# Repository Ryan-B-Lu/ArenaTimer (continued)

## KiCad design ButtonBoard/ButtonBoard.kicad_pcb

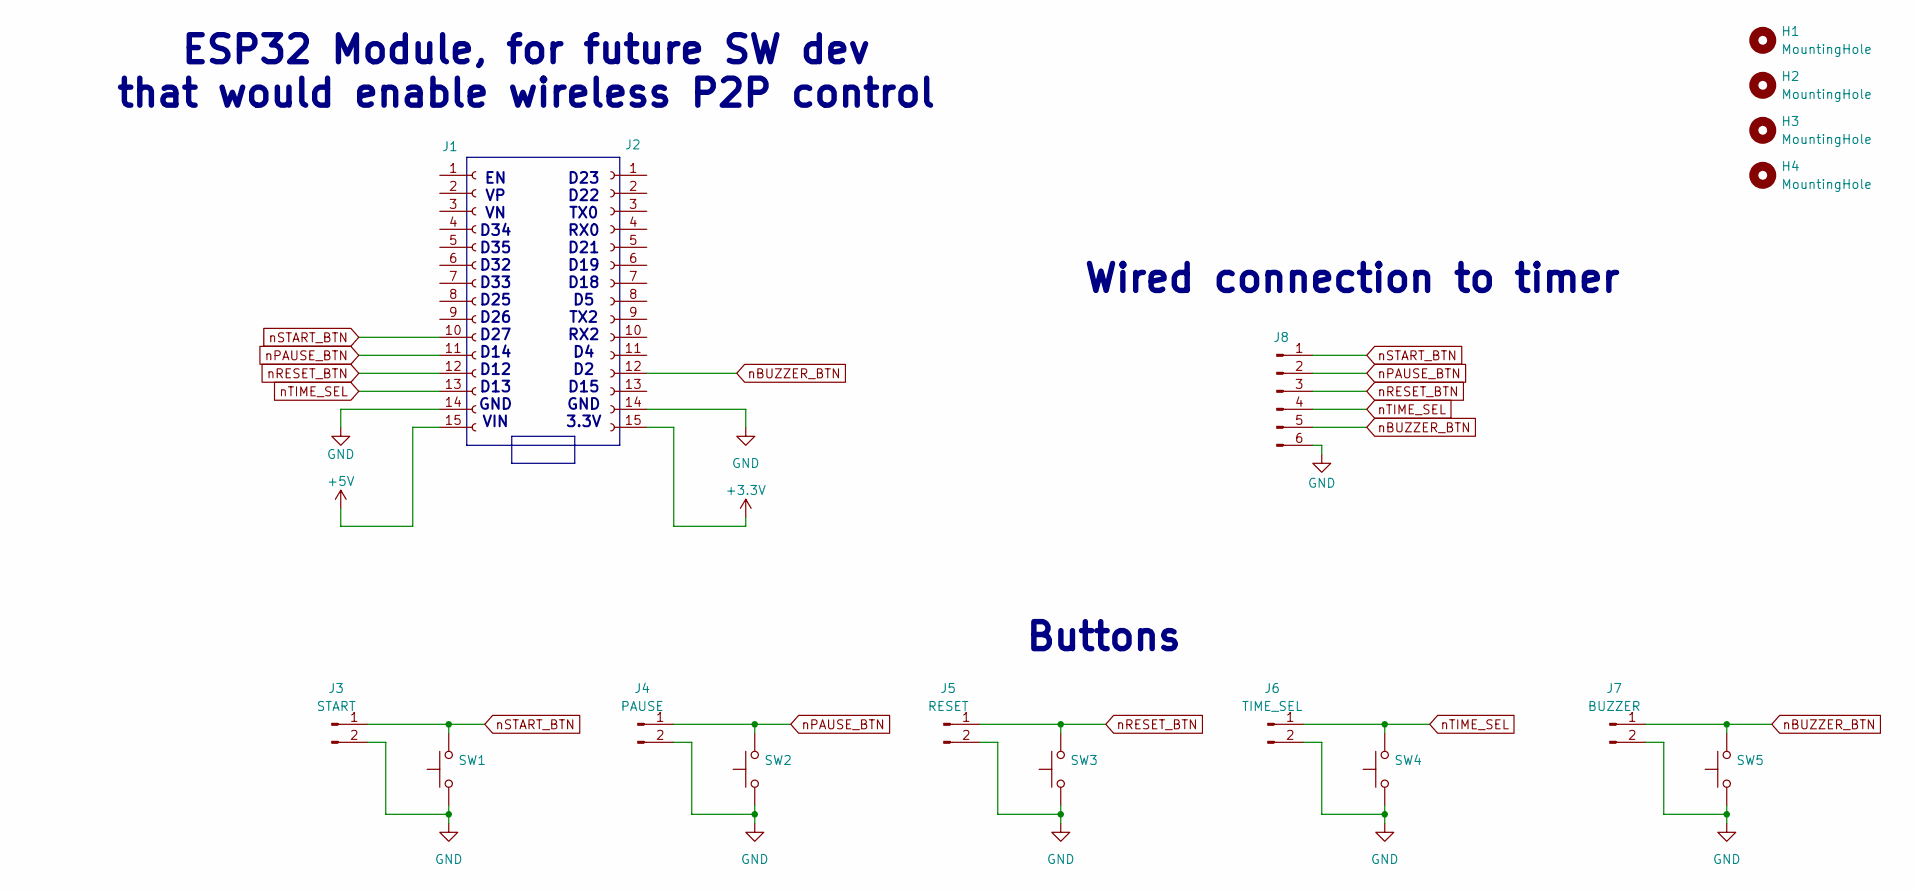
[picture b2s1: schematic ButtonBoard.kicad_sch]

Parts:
H1, H2, H3, H4: MountingHole; MountingHole_3.2mm_M3
J1, J2: Conn_01x15_Socket; PinSocket_1x15_P2.54mm_Vertical; LCSC C124408
J3: START; PinHeader_1x02_P2.54mm_Vertical
J4: PAUSE; PinHeader_1x02_P2.54mm_Vertical
J5: RESET; PinHeader_1x02_P2.54mm_Vertical
J6: TIME_SEL; PinHeader_1x02_P2.54mm_Vertical
J7: BUZZER; PinHeader_1x02_P2.54mm_Vertical
J8: Conn_01x06_Pin; JST_EH_S6B-EH_1x06_P2.50mm_Horizontal
SW1: START; SW_PUSH-12mm; LCSC C5377619
SW2: PAUSE; SW_PUSH-12mm; LCSC C5377619
SW3: RESET; SW_PUSH-12mm; LCSC C5377619
SW4: TIME_SEL; SW_PUSH-12mm; LCSC C5377619
SW5: BUZZER; SW_PUSH-12mm; LCSC C5377619

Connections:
+3.3V: J2.15
+5V: J1.15
GND: J1.14, J2.14, J3.2, J4.2, J5.2, J6.2, J7.2, J8.6, SW1.1, SW2.1, SW3.1, SW4.1, SW5.1
nBUZZER_BTN: J2.12, J7.1, J8.5, SW5.2
nPAUSE_BTN: J1.11, J4.1, J8.2, SW2.2
nRESET_BTN: J1.12, J5.1, J8.3, SW3.2
nSTART_BTN: J1.10, J3.1, J8.1, SW1.2
nTIME_SEL: J1.13, J6.1, J8.4, SW4.2

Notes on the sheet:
ESP32 Module, for future SW dev that would enable wireless P2P control
D23 D22 TX0 RX0 D21 D19 D18 D5 TX2 RX2 D4 D2 D15 GND 3.3V
Wired connection to timer
Buttons
EN VP VN D34 D35 D32 D33 D25 D26 D27 D14 D12 D13 GND VIN

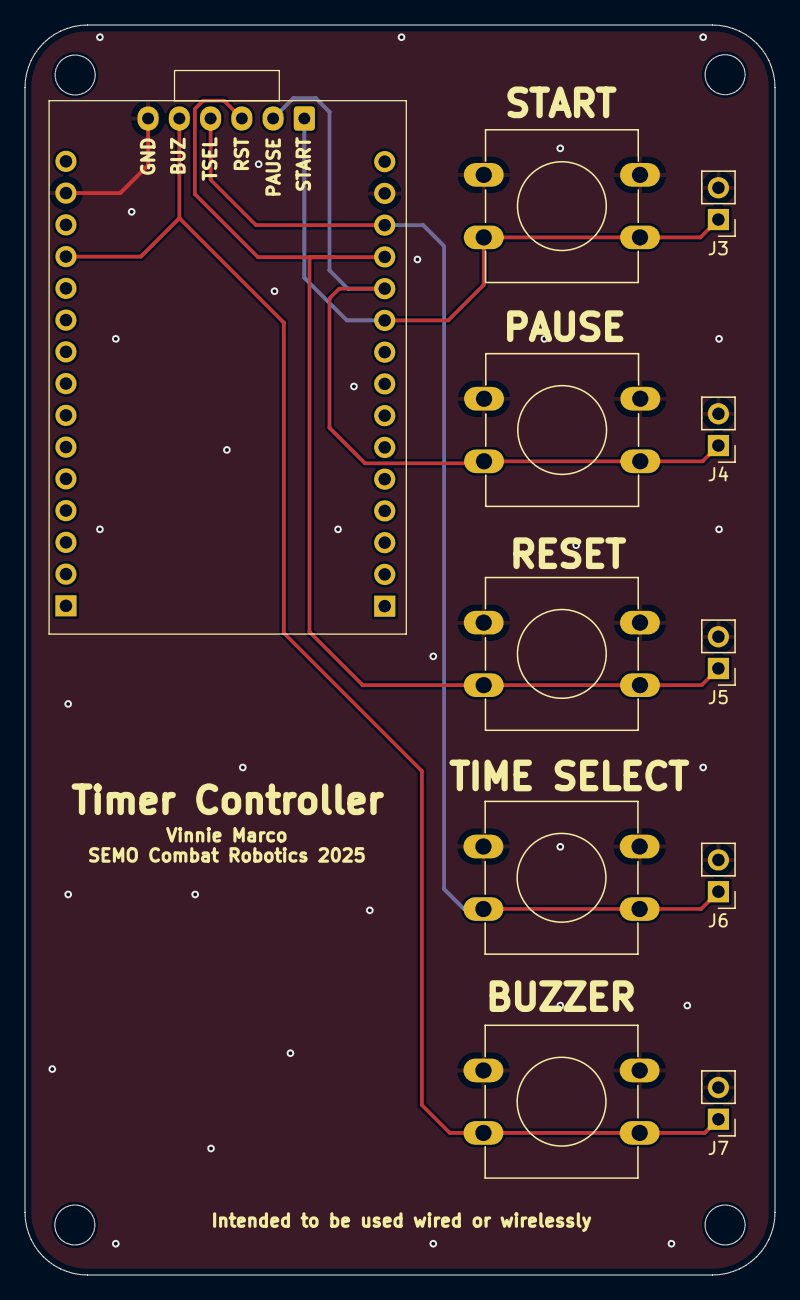
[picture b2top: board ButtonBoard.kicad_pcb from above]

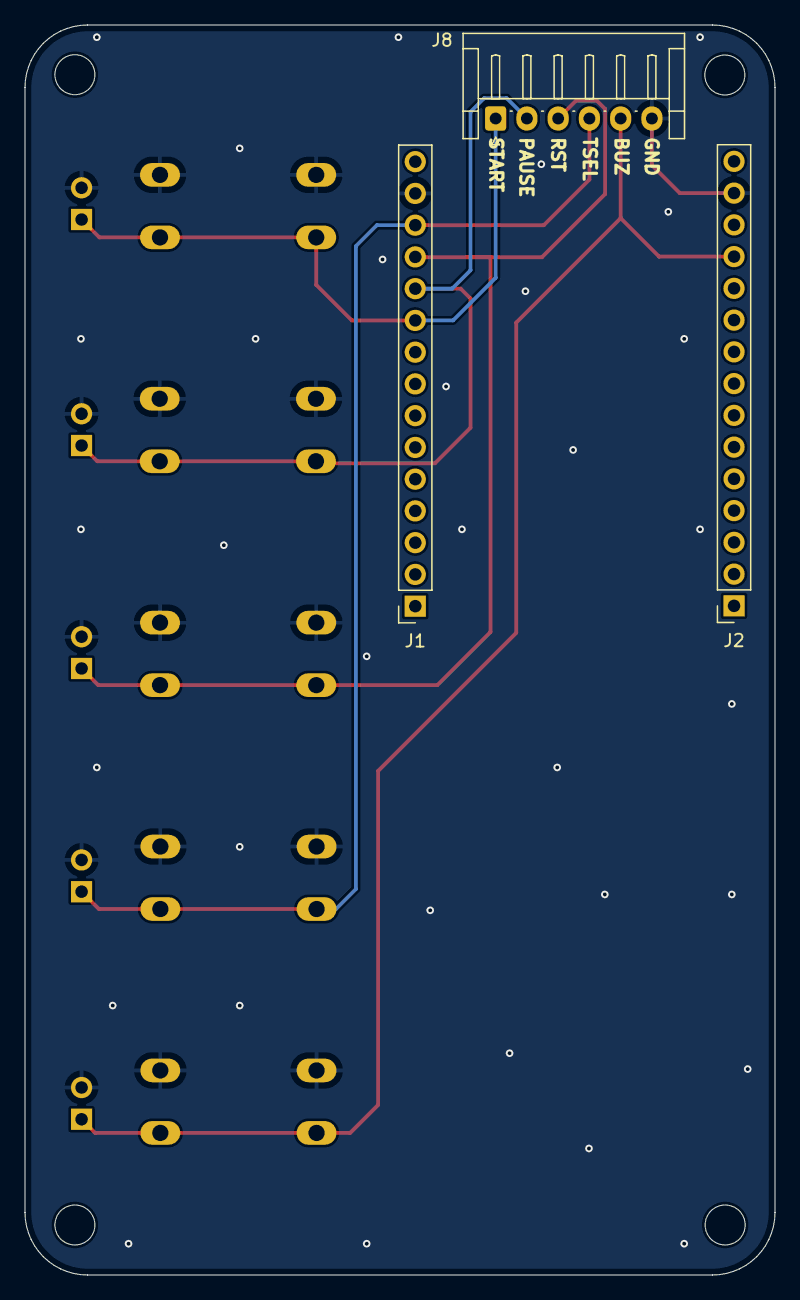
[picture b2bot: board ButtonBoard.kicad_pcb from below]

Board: 2 copper layers, 60.0 x 100.0 mm, 17 parts (3 on the bottom side), 6 nets.

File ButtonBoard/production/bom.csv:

Designator,Footprint,Quantity,Value,LCSC Part #
"J1, J2",PinSocket_1x15_P2.54mm_Vertical,2,Conn_01x15_Socket,C124408
J3,PinHeader_1x02_P2.54mm_Vertical,1,START,
J4,PinHeader_1x02_P2.54mm_Vertical,1,PAUSE,
J5,PinHeader_1x02_P2.54mm_Vertical,1,RESET,
J6,PinHeader_1x02_P2.54mm_Vertical,1,TIME_SEL,
J7,PinHeader_1x02_P2.54mm_Vertical,1,BUZZER,
J8,JST_EH_S6B-EH_1x06_P2.50mm_Horizontal,1,Conn_01x06_Pin,
SW1,SW_PUSH-12mm,1,START,C5377619
SW2,SW_PUSH-12mm,1,PAUSE,C5377619
SW3,SW_PUSH-12mm,1,RESET,C5377619
SW4,SW_PUSH-12mm,1,TIME_SEL,C5377619
SW5,SW_PUSH-12mm,1,BUZZER,C5377619

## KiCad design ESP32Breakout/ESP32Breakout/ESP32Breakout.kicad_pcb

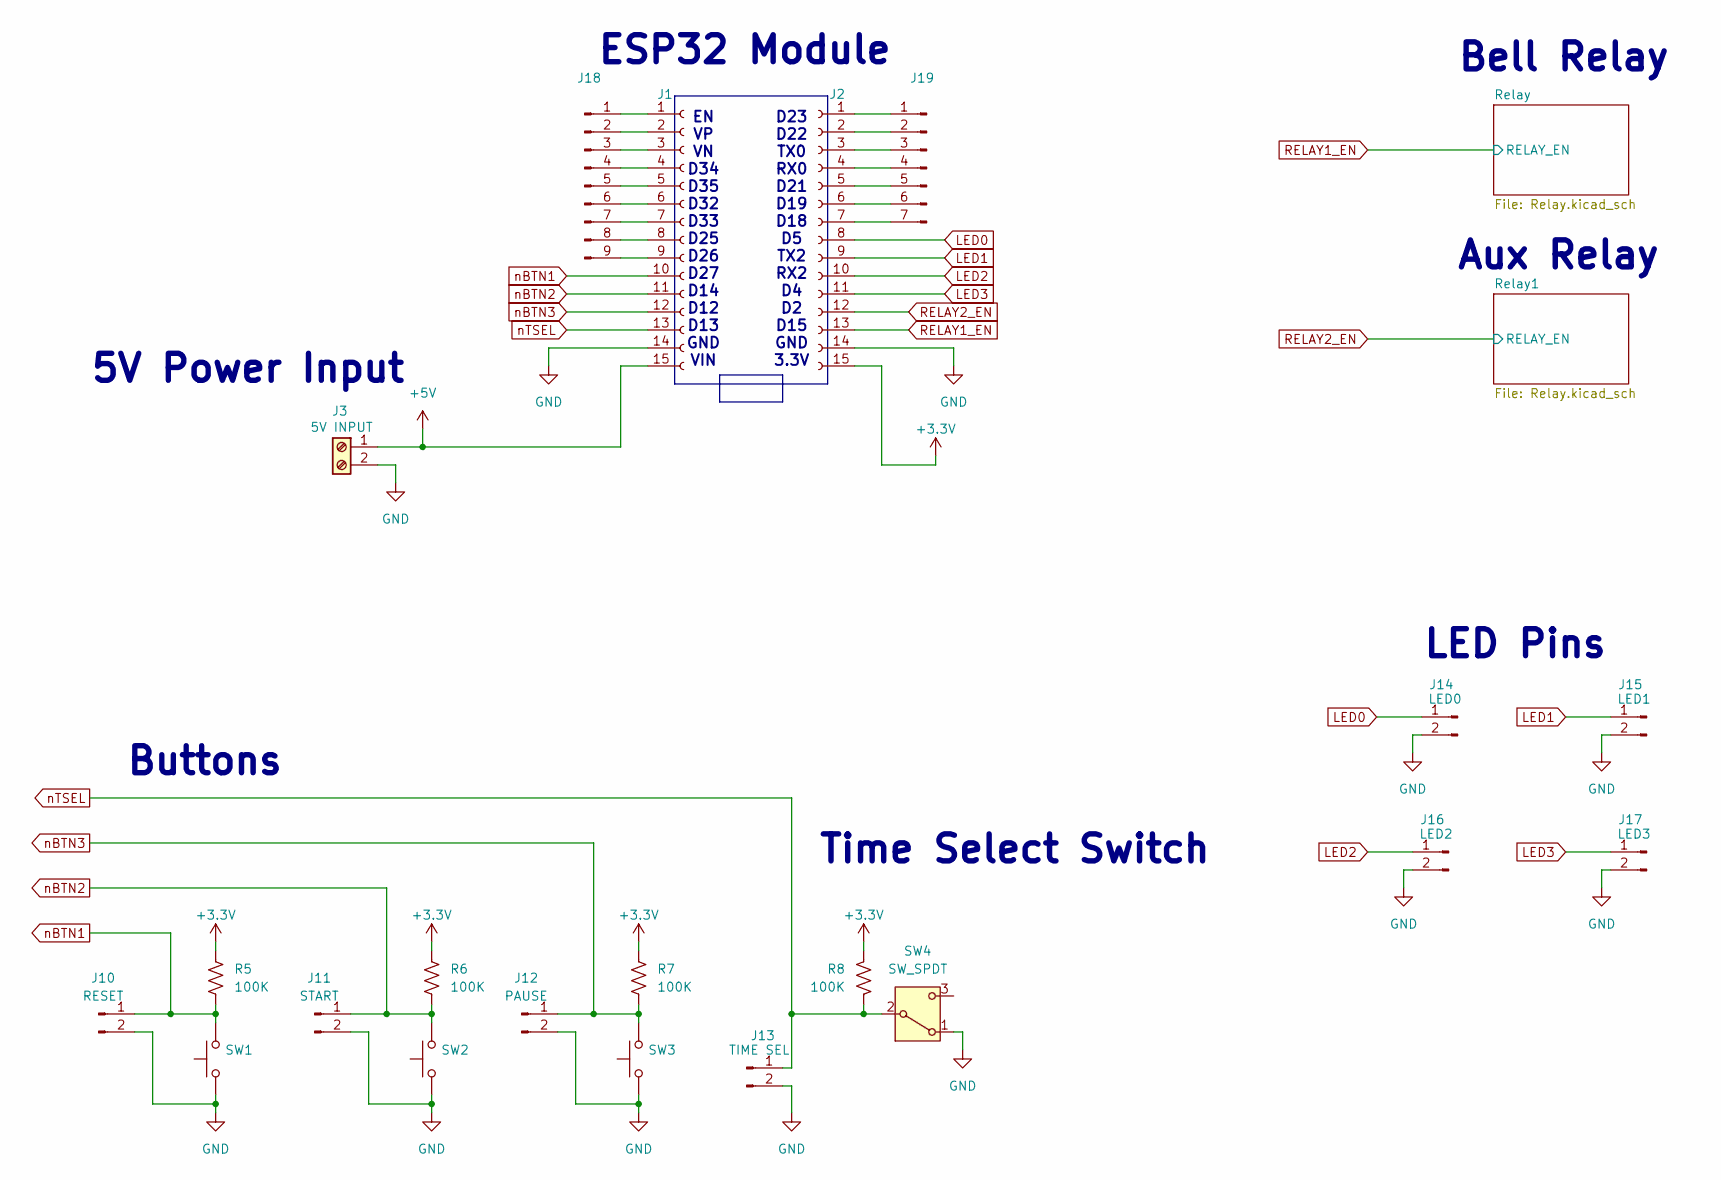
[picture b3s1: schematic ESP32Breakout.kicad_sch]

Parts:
J1, J2: Conn_01x15_Socket; PinHeader_1x15_P2.54mm_Vertical; LCSC C124408
J3: 5V INPUT; TerminalBlock_bornier-2_P5.08mm; LCSC C5142622
J10: RESET; PinHeader_1x02_P2.54mm_Vertical
J11: START; PinHeader_1x02_P2.54mm_Vertical
J12: PAUSE; PinHeader_1x02_P2.54mm_Vertical
J13: TIME SEL; PinHeader_1x02_P2.54mm_Vertical
J14: LED0; PinHeader_1x02_P2.54mm_Vertical; LCSC C124375
J15: LED1; PinHeader_1x02_P2.54mm_Vertical; LCSC C124375
J16: LED2; PinHeader_1x02_P2.54mm_Vertical; LCSC C124375
J17: LED3; PinHeader_1x02_P2.54mm_Vertical; LCSC C124375
J18: Conn_01x09_Pin; PinHeader_1x09_P2.54mm_Vertical
J19: Conn_01x07_Pin; PinHeader_1x07_P2.54mm_Vertical
R5, R6, R7, R8: 100K; R_0402_1005Metric; LCSC C25530
SW1: RESET; SW_PUSH-12mm; LCSC C5377619
SW2: START; SW_PUSH-12mm; LCSC C5377619
SW3: PAUSE; SW_PUSH-12mm; LCSC C5377619
SW4: SW_SPDT; SW_CK_JS202011AQN_DPDT_Angled; LCSC C223857

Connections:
+3.3V: J2.15, R5.1, R6.1, R7.1, R8.1
+5V: J1.15, J3.1; also elsewhere on the board
GND: J1.14, J2.14, J3.2, J10.2, J11.2, J12.2, J13.2, J14.2, J15.2, J16.2, J17.2, SW1.1, SW2.1, SW3.1, SW4.1 (A); also elsewhere on the board
LED0: J2.8, J14.1
LED1: J2.9, J15.1
LED2: J2.10, J16.1
LED3: J2.11, J17.1
unnamed: J1.1, J18.1
unnamed: J1.2, J18.2
unnamed: J1.3, J18.3
unnamed: J1.4, J18.4
unnamed: J1.5, J18.5
unnamed: J1.6, J18.6
unnamed: J1.7, J18.7
unnamed: J1.8, J18.8
unnamed: J1.9, J18.9
unnamed: J2.1, J19.1
unnamed: J2.2, J19.2
unnamed: J2.3, J19.3
unnamed: J2.4, J19.4
unnamed: J2.5, J19.5
unnamed: J2.6, J19.6
unnamed: J2.7, J19.7
RELAY1_EN: J2.13; also elsewhere on the board
RELAY2_EN: J2.12; also elsewhere on the board
nBTN1: J1.10, J10.1, R5.2, SW1.2
nBTN2: J1.11, J11.1, R6.2, SW2.2
nBTN3: J1.12, J12.1, R7.2, SW3.2
nTSEL: J1.13, J13.1, R8.2, SW4.2 (B)

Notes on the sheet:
Time Select Switch
5V Power Input
ESP32 Module
EN VP VN D34 D35 D32 D33 D25 D26 D27 D14 D12 D13 GND VIN
LED Pins
Bell Relay
D23 D22 TX0 RX0 D21 D19 D18 D5 TX2 RX2 D4 D2 D15 GND 3.3V
Aux Relay
Buttons

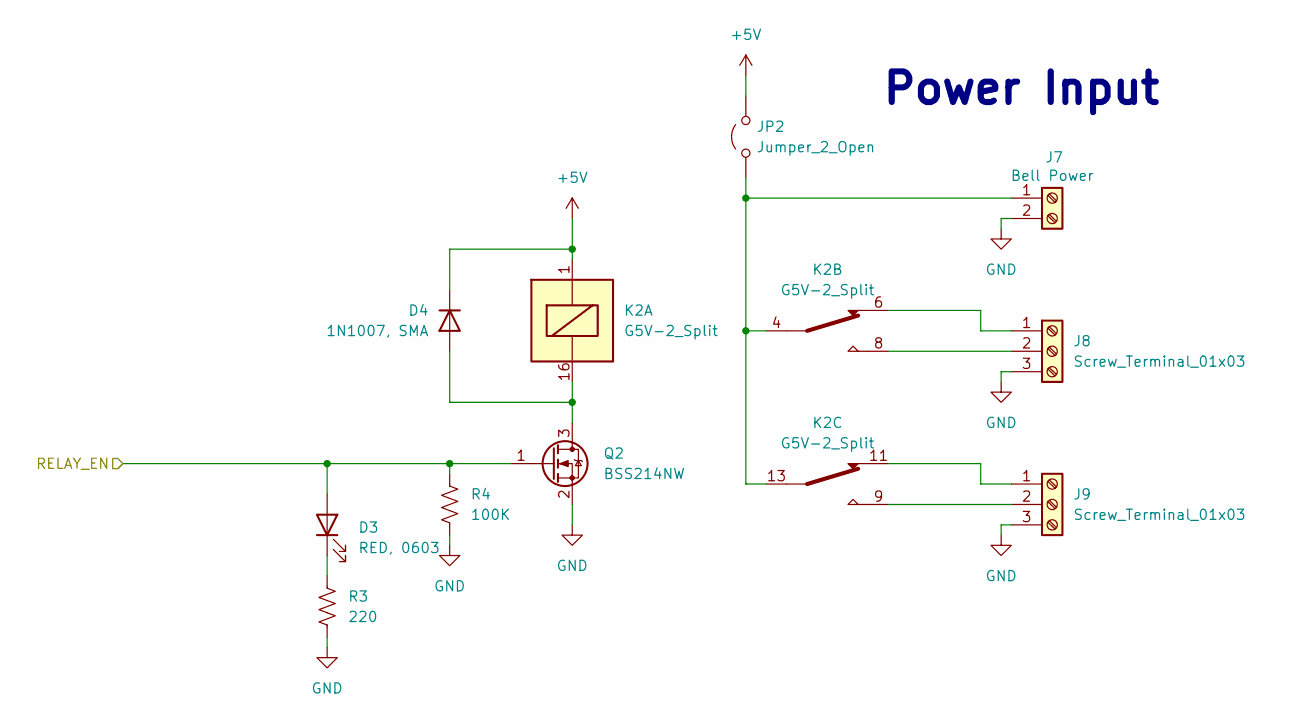
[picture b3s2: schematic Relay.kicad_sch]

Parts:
D3: RED, 0603; LED_0603_1608Metric; LCSC C2286
D4: 1N1007, SMA; D_SMA; LCSC C727081
J7: Bell Power; TerminalBlock_bornier-2_P5.08mm; LCSC C5142622
J8, J9: Screw_Terminal_01x03; TerminalBlock_bornier-3_P5.08mm; LCSC C5142621
JP2: Jumper_2_Open; SolderJumper-2_P1.3mm_Open_RoundedPad1.0x1.5mm
K2: G5V-2_Split; Relay_DPDT_Omron_G5V-2; LCSC C27269
Q2: BSS214NW; SOT-323_SC-70; LCSC C412741
R3: 220; R_0402_1005Metric; LCSC C25091
R4: 100K; R_0402_1005Metric; LCSC C25530

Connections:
+5V: D4.1 (K), JP2.2 (B), K2.1; also elsewhere on the board
GND: J7.2, J8.3, J9.3, Q2.2 (S), R3.2, R4.2; also elsewhere on the board
unnamed: D3.1 (K), R3.1
unnamed: D4.2 (A), K2.16, Q2.3 (D)
unnamed: J7.1, JP2.1 (A), K2.4, K2.13
unnamed: J8.1, K2.6
unnamed: J8.2, K2.8
unnamed: J9.1, K2.11
unnamed: J9.2, K2.9
RELAY2_EN: D3.2 (A), Q2.1 (G), R4.1; also elsewhere on the board

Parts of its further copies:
D1: RED, 0603; LED_0603_1608Metric; LCSC C2286
D2: 1N1007, SMA; D_SMA; LCSC C727081
J4: Bell Power; TerminalBlock_bornier-2_P5.08mm; LCSC C5142622
J5, J6: Screw_Terminal_01x03; TerminalBlock_bornier-3_P5.08mm; LCSC C5142621
JP1: Jumper_2_Open; SolderJumper-2_P1.3mm_Open_RoundedPad1.0x1.5mm
K1: G5V-2_Split; Relay_DPDT_Omron_G5V-2; LCSC C27269
Q1: BSS214NW; SOT-323_SC-70; LCSC C412741
R1: 220; R_0402_1005Metric; LCSC C25091
R2: 100K; R_0402_1005Metric; LCSC C25530

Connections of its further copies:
+5V: D2.1 (K), JP1.2 (B), K1.1; also elsewhere on the board
GND: J4.2, J5.3, J6.3, Q1.2 (S), R1.2, R2.2; also elsewhere on the board
unnamed: D1.1 (K), R1.1
unnamed: D2.2 (A), K1.16, Q1.3 (D)
unnamed: J4.1, JP1.1 (A), K1.4, K1.13
unnamed: J5.1, K1.6
unnamed: J5.2, K1.8
unnamed: J6.1, K1.11
unnamed: J6.2, K1.9
RELAY1_EN: D1.2 (A), Q1.1 (G), R2.1; also elsewhere on the board

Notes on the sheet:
Power Input

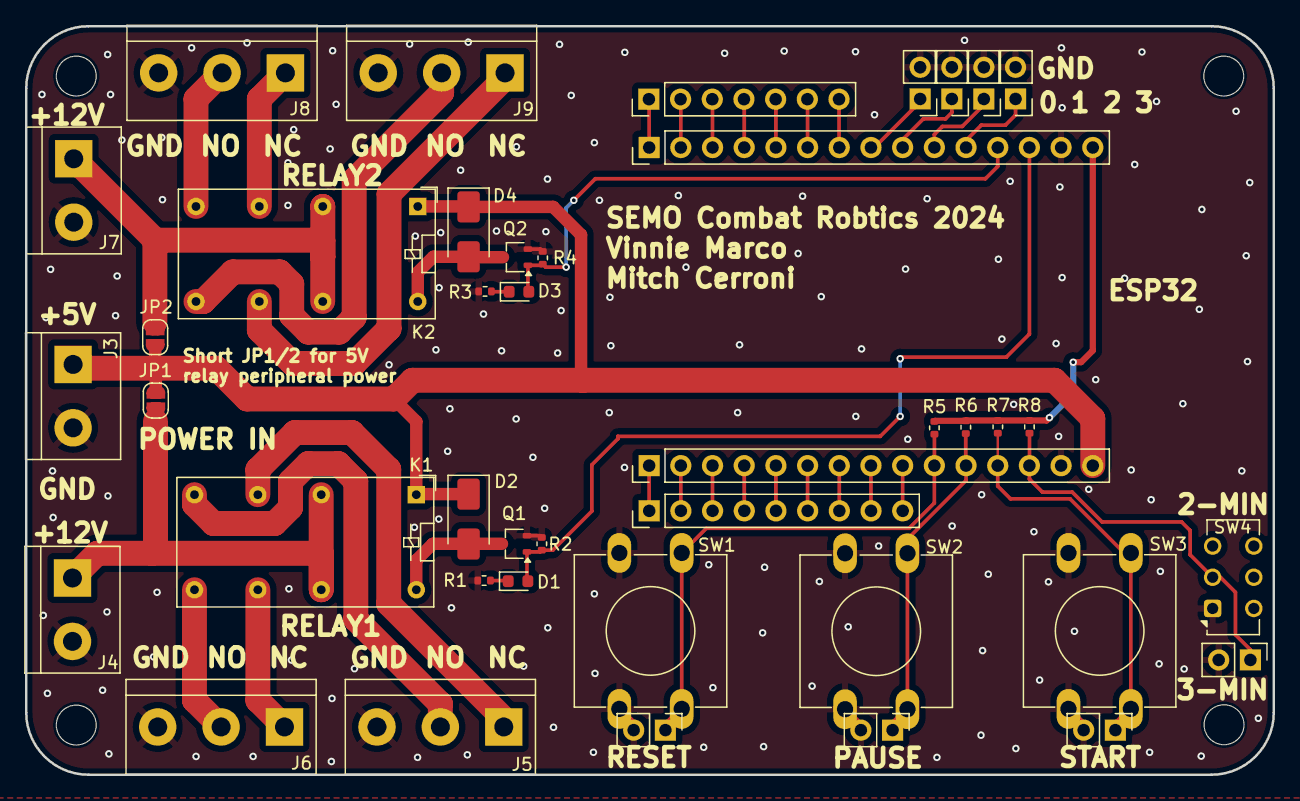
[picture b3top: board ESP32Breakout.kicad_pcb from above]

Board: 2 copper layers, 100.0 x 60.0 mm, 41 parts (0 on the bottom side), 43 nets.

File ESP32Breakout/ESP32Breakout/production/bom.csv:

Designator,Footprint,Quantity,Value,LCSC Part #
"D1, D3",0603,2,"RED, 0603", C2286
"D2, D4",D_SMA,2,"1N1007, SMA",C727081
"J1, J2",PinHeader_1x15_P2.54mm_Vertical,2,Conn_01x15_Socket,C124408
J13,PinHeader_1x02_P2.54mm_Vertical,1,TIME SEL,
J14,PinHeader_1x02_P2.54mm_Vertical,1,LED0,C124375
J15,PinHeader_1x02_P2.54mm_Vertical,1,LED1,C124375
J16,PinHeader_1x02_P2.54mm_Vertical,1,LED2,C124375
J17,PinHeader_1x02_P2.54mm_Vertical,1,LED3,C124375
J3,TerminalBlock_bornier-2_P5.08mm,1,5V INPUT,C5142622
"J4, J7",TerminalBlock_bornier-2_P5.08mm,2,Bell Power,C5142622
"J5, J6, J8, J9",TerminalBlock_bornier-3_P5.08mm,4,Screw_Terminal_01x03,C5142621
"JP1, JP2",SolderJumper-2_P1.3mm_Open_RoundedPad1.0x1.5mm,2,Jumper_2_Open,
"K1, K2",Relay_DPDT_Omron_G5V-2,2,G5V-2_Split,C27269
"Q1, Q2",SOT-323_SC-70,2,BSS214NW,C412741
"R1, R3",0402,2,220,C25091
"R2, R4, R5, R6, R7, R8",0402,6,100K,C25530
SW1,SW_PUSH-12mm,1,RESET,C5377619
SW2,SW_PUSH-12mm,1,START,C5377619
SW3,SW_PUSH-12mm,1,PAUSE,C5377619
SW4,SW_CK_JS202011AQN_DPDT_Angled,1,SW_SPDT,C223857

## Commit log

2024-11-26 inital commit with LED layout work started
2024-11-29 added digits
2024-12-02 finish up routing
2024-12-03 update board outline, generate production files
2024-12-03 create initial schematic for ESP32 board
2024-12-04 finished routing and DRC cleanup
2024-12-06 update production files for both boards
2025-02-22 add AP support for configuring network
2025-02-22 minor updates
2025-02-22 put correct file in directory
2025-03-16 add debouncing for external button handling to avoid external noise
2025-03-17 work on ready up functionality and 3 second countdown flashing
2025-03-17 working on match start countdown and border LEDs
2025-03-29 add 3d models
2025-04-07 playing with classes
2025-04-08 updated border animation
2025-04-08 fix animation, time keeping... Todo... add settings in browser
2025-04-08 started adding more web features
2025-04-09 update a few border corner cases
2025-05-01 push test code so I can work on other machine
2025-05-01 updated LED mapping to account for flipped pin, added web-control of ready up
2025-05-01 removed extra file
2025-05-05 PCB changes, code for TRC timers
2025-05-27 Fixed issue where timer wouldn't reset without pressing pause first.
    When I added protection around preventing reset during timer actively counting down, I forgot to put an exit case to the condition that allows reset when the timer has counted down
2025-05-28 add library dependencies for easier compliation
2025-05-28 upload 3d models, BOM, and assembly images
